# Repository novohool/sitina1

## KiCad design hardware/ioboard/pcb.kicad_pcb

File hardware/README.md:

# HARDWARE

This folder contains all the PCB design files and 3D models for the Sitina project.

## File List

* `auxiliary/` - Auxiliary PCB design files used for production testing, validation, and other purposes.
  * `jtag_adapter/` - A small JTAG adapter for connecting the IO board to a JTAG programmer.
  * `Resonant_V_validation/` - A separate board for testing the resonant V driver used in r0.11
  * `SR_V_validation/` - A separate board for testing the controlled slew-rate & dead-time V driver in r0.9
* `enclosure/` - 3D models for the enclosure in SolidWorks format.
* `gripflex/` - grip handle flexible PCB design files.
* `gripflex-lh/` - Left handed version
* `ioboard/` - IO board (power supply, routing, house keeping MCU, etc) PCB design files.
* `ioboard-lh/` - Left handed version
* `sensorboard/` - Latest Sensor board (CCD Sensor, AFE, H/V Driver, Controller) PCB design files
* `sensorboard-backport/` - Sensor board PCB design files. This version is a back port of r0.11 to r0.9. Uses the old H/V Drivers
* `pcb_common/` - Symbol and footprint libraries. This is a submodule link to: [pcb_common](https://gitlab.com/zephray/pcb_common)

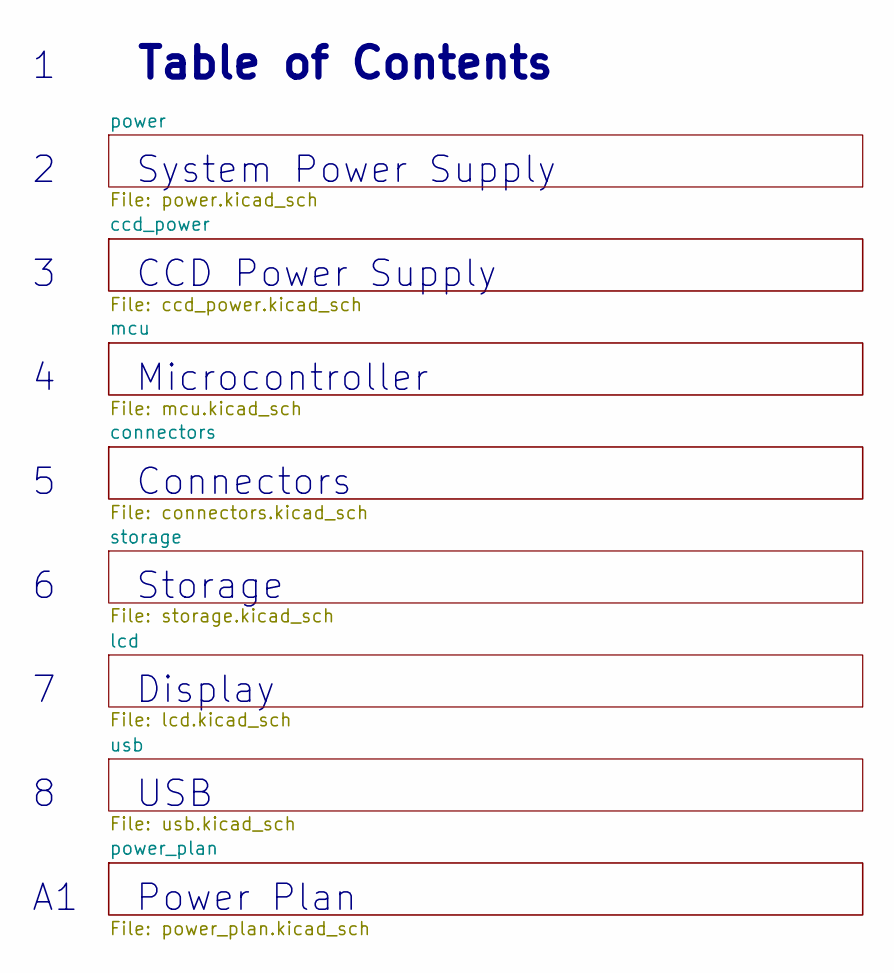
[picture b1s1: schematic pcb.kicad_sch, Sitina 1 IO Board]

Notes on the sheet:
CCD Power Supply
Power Plan
System Power Supply
Table of Contents
USB
Microcontroller
Display
Storage
Connectors

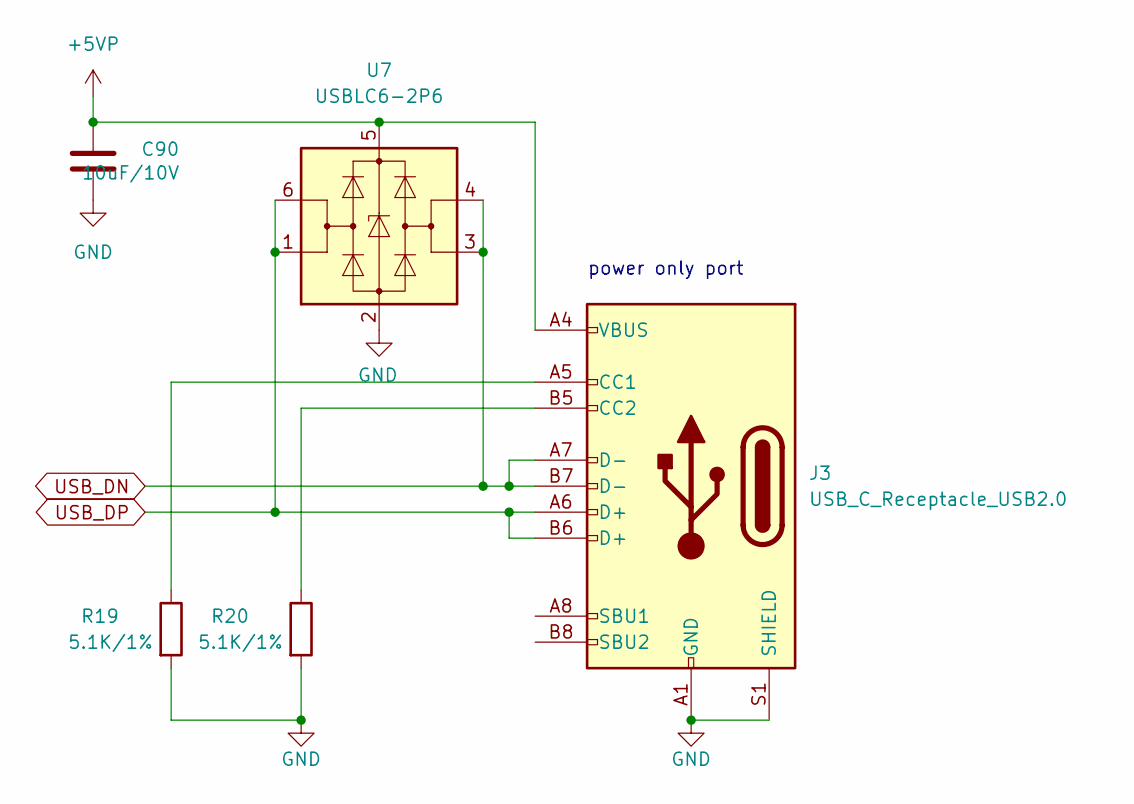
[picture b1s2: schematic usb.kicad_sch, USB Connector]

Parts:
C90: 10uF/10V; C_0603_1608Metric
J3: USB_C_Receptacle_USB2.0; USB_C_Receptacle_HRO_TYPE-C-31-M-12
R19, R20: 5.1K/1%; R_0402_1005Metric
U7: USBLC6-2P6; SOT-666

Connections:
+5VP: C90.1, J3.A4 (VBUS), J3.A9 (VBUS), J3.B4 (VBUS), J3.B9 (VBUS), U7.5 (VBUS); also elsewhere on the board
GND: C90.2, J3.A1 (GND), J3.A12 (GND), J3.B1 (GND), J3.B12 (GND), J3.S1 (SHIELD), R19.2, R20.2, U7.2 (GND); also elsewhere on the board
unnamed: J3.A5 (CC1), R19.1
unnamed: J3.B5 (CC2), R20.1
USB_DN: J3.A7 (D-), J3.B7 (D-), U7.3 (I/O2), U7.4 (I/O2); also elsewhere on the board
USB_DP: J3.A6 (D+), J3.B6 (D+), U7.1 (I/O1), U7.6 (I/O1); also elsewhere on the board

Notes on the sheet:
power only port

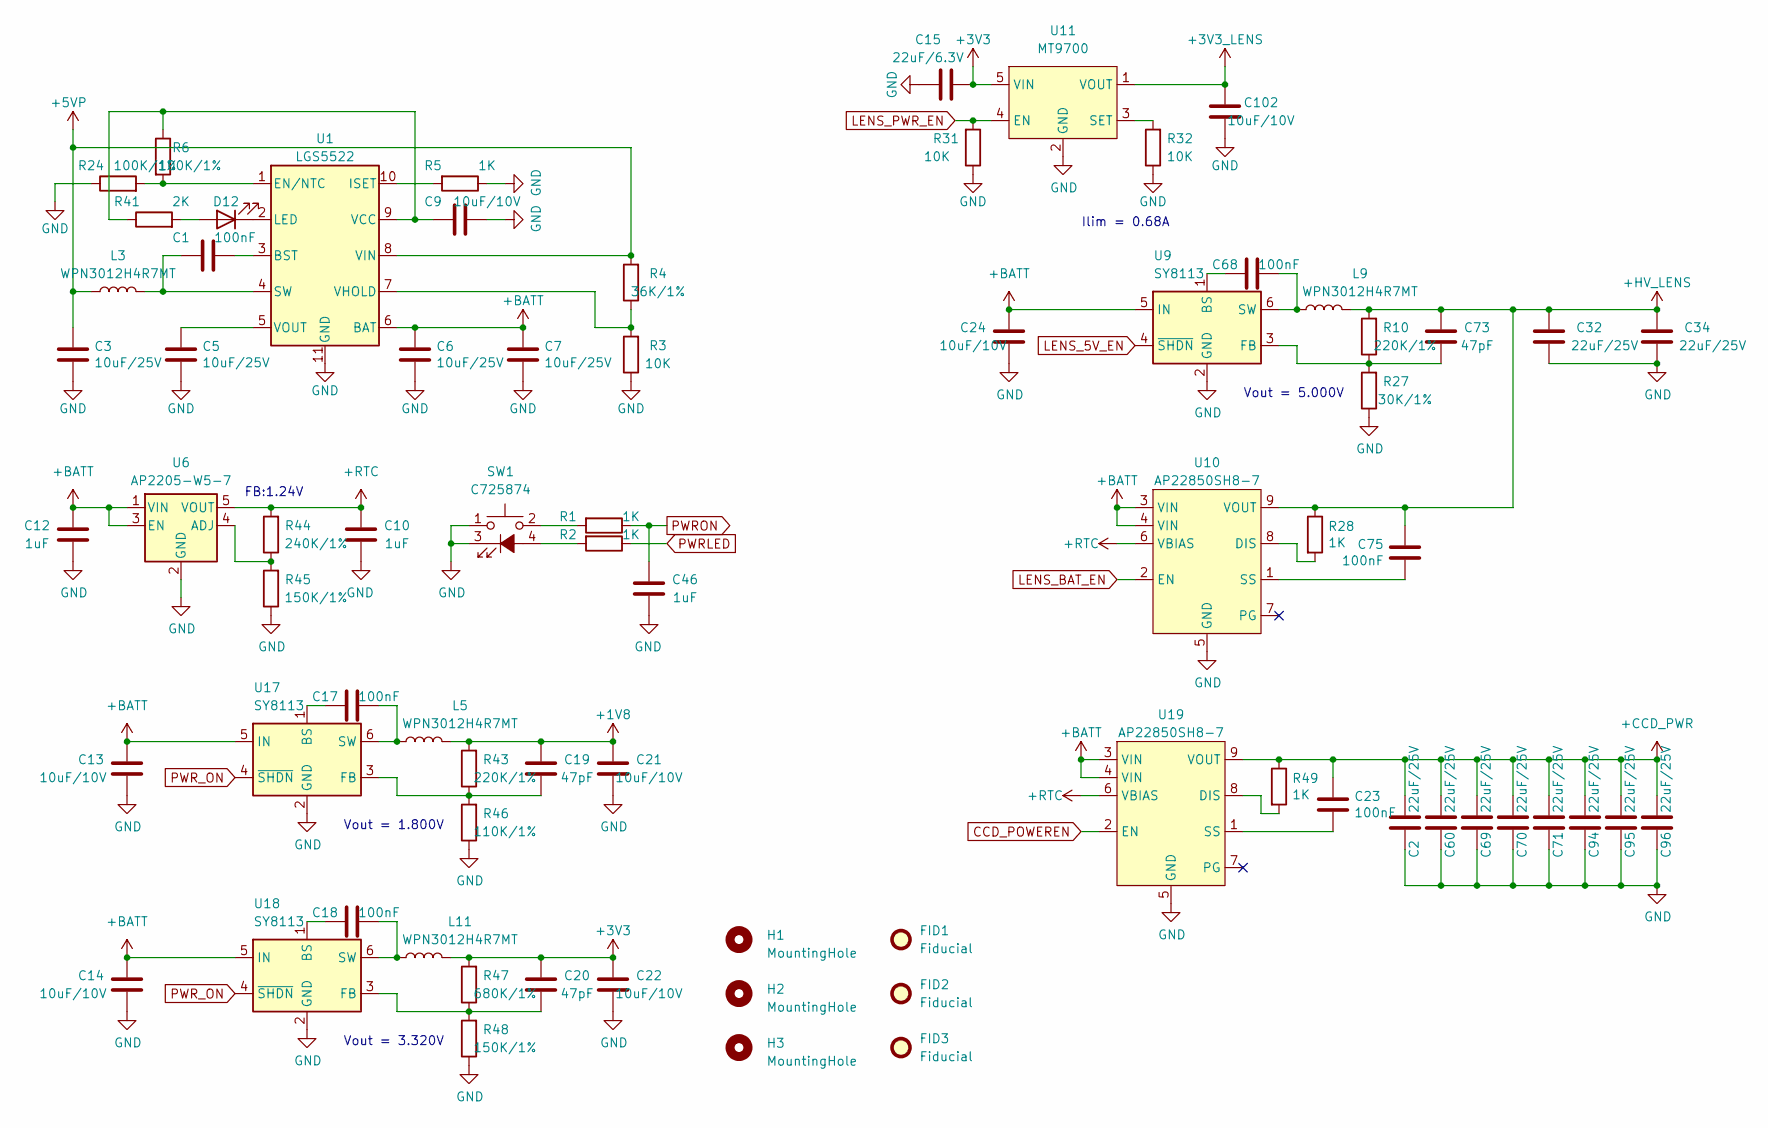
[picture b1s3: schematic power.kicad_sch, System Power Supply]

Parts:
C1, C17, C18, C23, C68, C75: 100nF; C_0402_1005Metric
C2, C32, C34, C60, C69, C70, C71, C94, C95, C96: 22uF/25V; C_1206_3216Metric
C3, C5, C6, C7: 10uF/25V; C_0805_2012Metric
C9, C13, C14, C21, C22, C24, C102: 10uF/10V; C_0603_1608Metric
C10, C12, C46: 1uF; C_0402_1005Metric
C15: 22uF/6.3V; C_0603_1608Metric
C19, C20, C73: 47pF; C_0402_1005Metric
D12: LED; LED_0603_1608Metric
FID1, FID2, FID3: Fiducial; Fiducial_0.75mm_Mask1.5mm
H1, H2, H3: MountingHole; MountingHole_2.2mm_M2_DIN965
L3, L5, L9, L11: WPN3012H4R7MT; L_Changjiang_FNR3012S
R1, R2, R5, R28, R49: 1K; R_0402_1005Metric
R3, R31, R32: 10K; R_0402_1005Metric
R4: 36K/1%; R_0402_1005Metric
R6, R24: 100K/1%; R_0402_1005Metric
R10, R43: 220K/1%; R_0402_1005Metric
R27: 30K/1%; R_0402_1005Metric
R41: 2K; R_0402_1005Metric
R44: 240K/1%; R_0402_1005Metric
R45, R48: 150K/1%; R_0402_1005Metric
R46: 110K/1%; R_0402_1005Metric
R47: 680K/1%; R_0402_1005Metric
SW1: C725874; TM-007-D1-X
U1: LGS5522; SSOP-10-1EP_3.9x4.9mm_P1mm_EP2.1x3.3mm
U6: AP2205-W5-7; SOT-23-5
U9, U17, U18: SY8113; TSOT-23-6
U10, U19: AP22850SH8-7; DFN-8-1EP_2x2mm_P0.5mm_EP0.9x1.6mm
U11: MT9700; SOT-23-5

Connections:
+1V8: C19.2, C21.2, L5.2, R43.2; also elsewhere on the board
+3V3: C15.1, C20.2, C22.2, L11.2, R47.2, U11.5 (VIN); also elsewhere on the board
+3V3_LENS: C102.1, U11.1 (VOUT); also elsewhere on the board
+5VP: C3.2, L3.1, R4.2, U1.8 (VIN); also elsewhere on the board
+BATT: C6.2, C7.2, C12.1, C13.2, C14.2, C24.2, U1.6 (BAT), U6.1 (VIN), U6.3 (EN), U9.5 (IN), U10.3 (VIN), U10.4 (VIN), U17.5 (IN), U18.5 (IN), U19.3 (VIN), U19.4 (VIN); also elsewhere on the board
+CCD_PWR: C2.1, C23.2, C60.1, C69.1, C70.1, C71.1, C94.1, C95.1, C96.1, R49.1, U19.9 (VOUT); also elsewhere on the board
+HV_LENS: C32.1, C34.1, C73.2, C75.2, L9.2, R10.2, R28.1, U10.9 (VOUT); also elsewhere on the board
+RTC: C10.1, R44.2, U6.5 (VOUT), U10.6 (VBIAS), U19.6 (VBIAS); also elsewhere on the board
CCD_POWEREN: U19.2 (EN); also elsewhere on the board
GND: C2.2, C3.1, C5.1, C6.1, C7.1, C9.1, C10.2, C12.2, C13.1, C14.1, C15.2, C21.1, C22.1, C24.1, C32.2, C34.2, C46.2, C60.2, C69.2, C70.2, C71.2, C94.2, C95.2, C96.2, C102.2, R3.1, R5.1, R24.1, R27.1, R31.1, R32.1, R45.1, R46.1, R48.1, SW1.1, SW1.3 (K), U1.11 (GND), U6.2 (GND), U9.2 (GND), U10.5 (GND), U11.2 (GND), U17.2 (GND), U18.2 (GND), U19.5 (GND); also elsewhere on the board
LENS_5V_EN: U9.4 (~SHDN); also elsewhere on the board
LENS_BAT_EN: U10.2 (EN); also elsewhere on the board
LENS_PWR_EN: R31.2, U11.4 (EN); also elsewhere on the board
unnamed: D12.2 (A), R41.2
unnamed: D12.1 (K), U1.2 (LED)
unnamed: R1.2, SW1.2
unnamed: R2.2, SW1.4 (A)
unnamed: C1.1, U1.3 (BST)
unnamed: R6.2, R24.2, U1.1 (EN/NTC)
unnamed: R5.2, U1.10 (ISET)
unnamed: C1.2, L3.2, U1.4 (SW)
unnamed: C9.2, R6.1, R41.1, U1.9 (VCC)
unnamed: R3.2, R4.1, U1.7 (VHOLD)
unnamed: C5.2, U1.5 (VOUT)
unnamed: R44.1, R45.2, U6.4 (ADJ)
unnamed: C68.2, U9.1 (BS)
unnamed: C73.1, R10.1, R27.2, U9.3 (FB)
unnamed: C68.1, L9.1, U9.6 (SW)
unnamed: R28.2, U10.8 (DIS)
unnamed: C75.1, U10.1 (SS)
unnamed: R32.2, U11.3 (SET)
unnamed: C17.2, U17.1 (BS)
unnamed: C19.1, R43.1, R46.2, U17.3 (FB)
unnamed: C17.1, L5.1, U17.6 (SW)
unnamed: C18.2, U18.1 (BS)
unnamed: C20.1, R47.1, R48.2, U18.3 (FB)
unnamed: C18.1, L11.1, U18.6 (SW)
unnamed: R49.2, U19.8 (DIS)
unnamed: C23.1, U19.1 (SS)
PWRLED: R2.1; also elsewhere on the board
PWRON: C46.1, R1.1; also elsewhere on the board
PWR_ON: U17.4 (~SHDN), U18.4 (~SHDN); also elsewhere on the board

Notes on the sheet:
Ilim = 0.68A
Vout = 1.800V
Vout = 3.320V
FB:1.24V
Vout = 5.000V

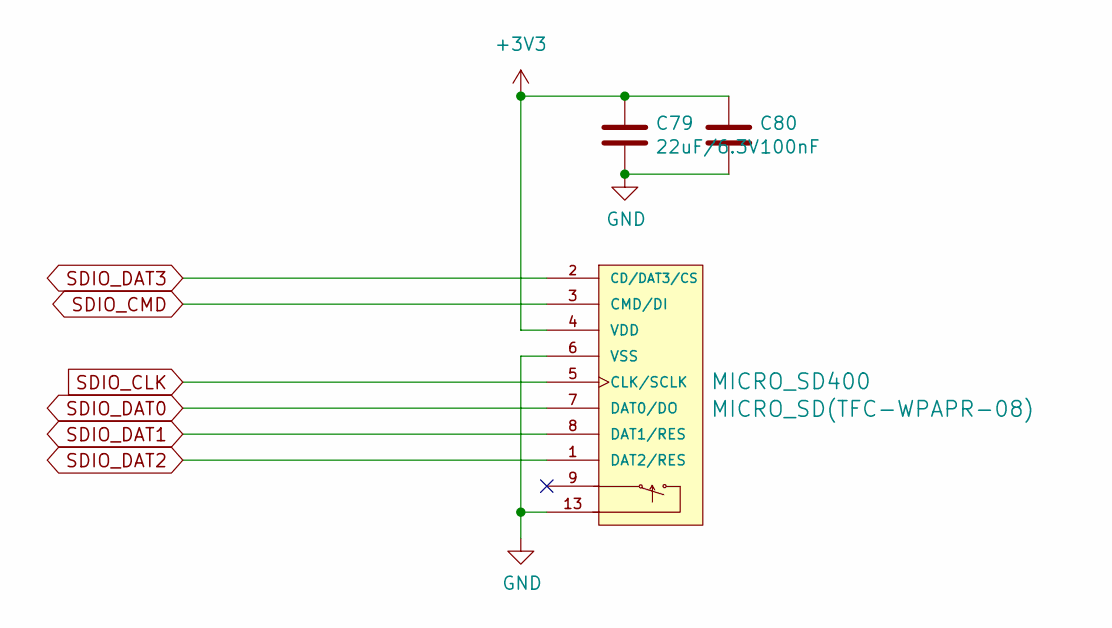
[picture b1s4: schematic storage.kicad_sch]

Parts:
C79: 22uF/6.3V; C_0603_1608Metric
C80: 100nF; C_0402_1005Metric
MICRO_SD400: MICRO_SD(TFC-WPAPR-08); TFC-WPAPR-08

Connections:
+3V3: C79.1, C80.1; also elsewhere on the board
GND: C79.2, C80.2; also elsewhere on the board

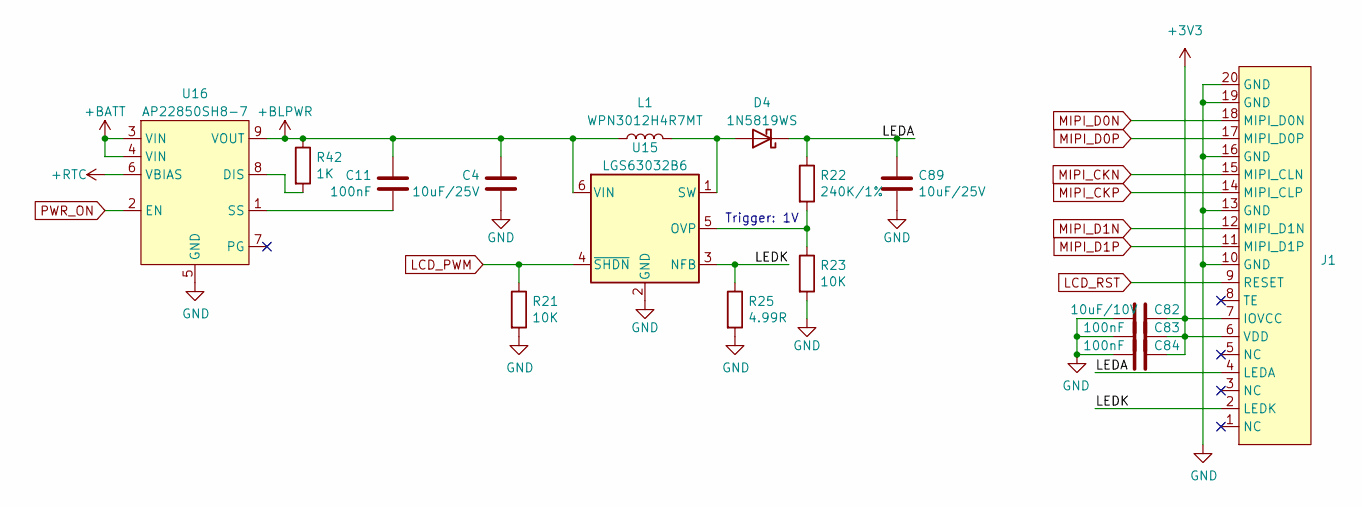
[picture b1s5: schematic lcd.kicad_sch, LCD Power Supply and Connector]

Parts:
C4, C89: 10uF/25V; C_0805_2012Metric
C11, C83, C84: 100nF; C_0402_1005Metric
C82: 10uF/10V; C_0603_1608Metric
D4: 1N5819WS; D_SOD-323
J1: Hirose_FH12-20S-0.5SH_1x20-1MP_P0.50mm_Horizontal_Reversed
L1: WPN3012H4R7MT; L_Changjiang_FNR3012S
R21, R23: 10K; R_0402_1005Metric
R22: 240K/1%; R_0402_1005Metric
R25: 4.99R; R_0402_1005Metric
R42: 1K; R_0402_1005Metric
U15: LGS63032B6; SOT-23-6
U16: AP22850SH8-7; DFN-8-1EP_2x2mm_P0.5mm_EP0.9x1.6mm

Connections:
+3V3: C82.2, C83.1, C84.1, J1.6 (VDD), J1.7 (IOVCC); also elsewhere on the board
+BATT: U16.3 (VIN), U16.4 (VIN); also elsewhere on the board
+BLPWR: C4.2, C11.2, L1.1, R42.1, U15.6 (VIN), U16.9 (VOUT)
+RTC: U16.6 (VBIAS); also elsewhere on the board
/lcd/LEDA: C89.2, D4.1 (K), J1.4 (LEDA), R22.1
/lcd/LEDK: J1.2 (LEDK), R25.1, U15.3 (NFB)
GND: C4.1, C82.1, C83.2, C84.2, C89.1, J1.10 (GND), J1.13 (GND), J1.16 (GND), J1.19 (GND), J1.20 (GND), R21.2, R23.2, R25.2, U15.2 (GND), U16.5 (GND); also elsewhere on the board
LCD_PWM: R21.1, U15.4 (~SHDN); also elsewhere on the board
LCD_RST: J1.9 (RESET); also elsewhere on the board
MIPI_CKN: J1.15 (MIPI_CLN); also elsewhere on the board
MIPI_CKP: J1.14 (MIPI_CLP); also elsewhere on the board
MIPI_D0N: J1.18 (MIPI_D0N); also elsewhere on the board
MIPI_D0P: J1.17 (MIPI_D0P); also elsewhere on the board
MIPI_D1N: J1.12 (MIPI_D1N); also elsewhere on the board
MIPI_D1P: J1.11 (MIPI_D1P); also elsewhere on the board
unnamed: D4.2 (A), L1.2, U15.1 (SW)
unnamed: R22.2, R23.1, U15.5 (OVP)
unnamed: R42.2, U16.8 (DIS)
unnamed: C11.1, U16.1 (SS)
PWR_ON: U16.2 (EN); also elsewhere on the board

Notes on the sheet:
Trigger: 1V

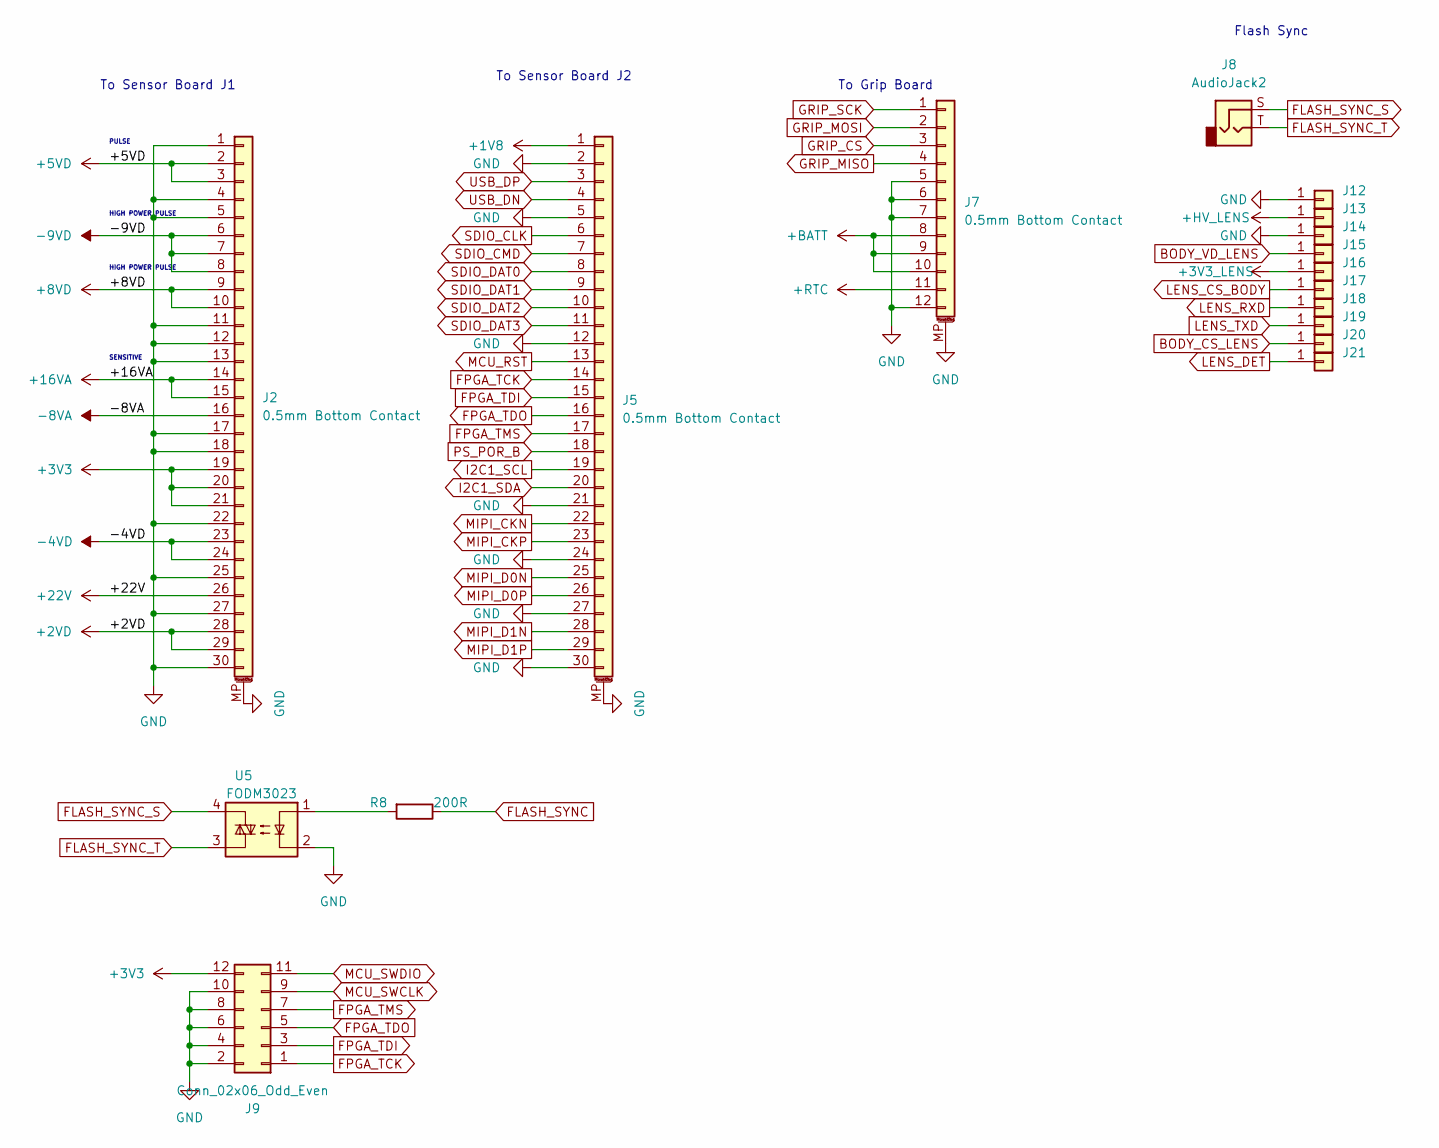
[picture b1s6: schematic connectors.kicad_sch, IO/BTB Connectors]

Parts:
J2, J5: 0.5mm Bottom Contact; Hirose_FH12-30S-0.5SH_1x30-1MP_P0.50mm_Horizontal
J7: 0.5mm Bottom Contact; Hirose_FH12-12S-0.5SH_1x12-1MP_P0.50mm_Horizontal
J8: AudioJack2; Jack_2.5mm_PJ_210A
J9: Conn_02x06_Odd_Even; PinSocket_2x06_P1.27mm_Horizontal
J12, J13, J14, J15, J16, J17, J18, J19, J20, J21: LensMount; YZP0652-15072-01
R8: 200R; R_0402_1005Metric
U5: FODM3023; MFP4_3.85x4.4

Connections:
+1V8: J5.1; also elsewhere on the board
+2VD: J2.28, J2.29; also elsewhere on the board
+3V3: J2.19, J2.20, J2.21, J9.12; also elsewhere on the board
+3V3_LENS: J16.1; also elsewhere on the board
+5VD: J2.2, J2.3; also elsewhere on the board
+8VD: J2.9, J2.10; also elsewhere on the board
+16VA: J2.14, J2.15; also elsewhere on the board
+22V: J2.26; also elsewhere on the board
+BATT: J7.8, J7.9, J7.10; also elsewhere on the board
+HV_LENS: J13.1; also elsewhere on the board
+RTC: J7.11; also elsewhere on the board
-4VD: J2.23, J2.24; also elsewhere on the board
-8VA: J2.16; also elsewhere on the board
-9VD: J2.6, J2.7, J2.8; also elsewhere on the board
BODY_CS_LENS: J20.1; also elsewhere on the board
BODY_VD_LENS: J15.1; also elsewhere on the board
FLASH_SYNC: R8.1; also elsewhere on the board
FLASH_SYNC_S: J8.S, U5.4
FLASH_SYNC_T: J8.T, U5.3
FPGA_TCK: J5.14, J9.1
FPGA_TDI: J5.15, J9.3
FPGA_TDO: J5.16, J9.5
FPGA_TMS: J5.17, J9.7
GND: J2.1, J2.4, J2.5, J2.11, J2.12, J2.13, J2.17, J2.18, J2.22, J2.25, J2.27, J2.30, J2.MP (MountPin), J5.2, J5.5, J5.12, J5.21, J5.24, J5.27, J5.30, J5.MP (MountPin), J7.5, J7.6, J7.7, J7.12, J7.MP (MountPin), J9.2, J9.4, J9.6, J9.8, J9.10, J12.1, J14.1, U5.2; also elsewhere on the board
GRIP_CS: J7.3; also elsewhere on the board
GRIP_MISO: J7.4; also elsewhere on the board
GRIP_MOSI: J7.2; also elsewhere on the board
GRIP_SCK: J7.1; also elsewhere on the board
I2C1_SCL: J5.19; also elsewhere on the board
I2C1_SDA: J5.20; also elsewhere on the board
LENS_CS_BODY: J17.1; also elsewhere on the board
LENS_DET: J21.1; also elsewhere on the board
LENS_RXD: J18.1; also elsewhere on the board
LENS_TXD: J19.1; also elsewhere on the board
MCU_BOOT: J9.9; also elsewhere on the board
MCU_RST: J5.13; also elsewhere on the board
MCU_SWDIO: J9.11; also elsewhere on the board
MIPI_CKN: J5.22; also elsewhere on the board
MIPI_CKP: J5.23; also elsewhere on the board
MIPI_D0N: J5.25; also elsewhere on the board
MIPI_D0P: J5.26; also elsewhere on the board
MIPI_D1N: J5.28; also elsewhere on the board
MIPI_D1P: J5.29; also elsewhere on the board
unnamed: R8.2, U5.1
PS_POR_B: J5.18; also elsewhere on the board
SDIO_CLK: J5.6; also elsewhere on the board
SDIO_CMD: J5.7; also elsewhere on the board
SDIO_DAT0: J5.8; also elsewhere on the board
SDIO_DAT1: J5.9; also elsewhere on the board
SDIO_DAT2: J5.10; also elsewhere on the board
SDIO_DAT3: J5.11; also elsewhere on the board
USB_DN: J5.4; also elsewhere on the board
USB_DP: J5.3; also elsewhere on the board

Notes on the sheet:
PULSE
To Sensor Board J2
To Grip Board
To Sensor Board J1
Flash Sync
SENSITIVE
HIGH POWER PULSE

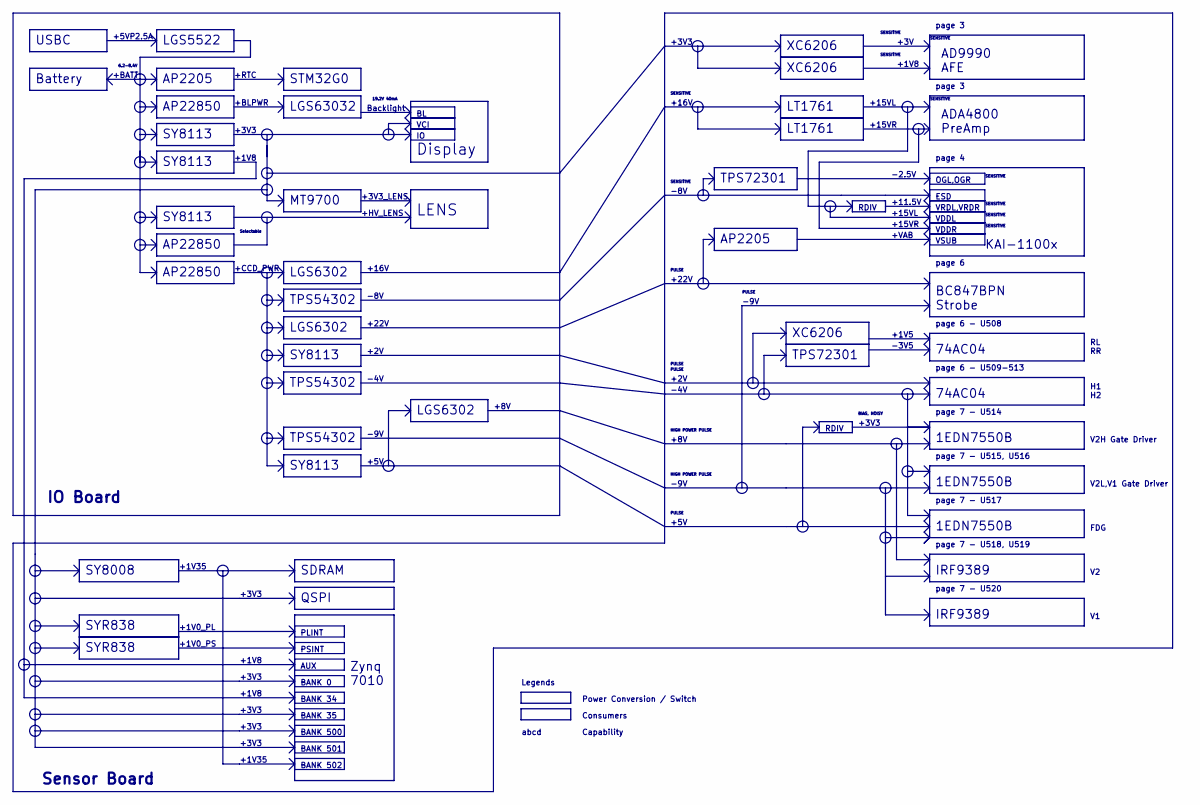
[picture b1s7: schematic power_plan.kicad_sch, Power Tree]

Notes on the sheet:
MT9700
page 7 - U515, U516
+16V
+3V3
SENSITIVE
HIGH POWER PULSE
+1V8
+15VL
page 6 - U508
+1V0_PL
+15VR
Consumers
LGS5522
SY8113
TPS54302
VCI
PLINT
STM32G0
+1V5
+RTC
2.5A
page 6 - U509-513
ESD
-9V
VDDR
LT1761
BANK 501
Legends
+8V
Zynq 7010
+CCD_PWR
+1V35
6.2-8.4V
+2V
Capability
LGS6302
PULSE
-4V
1EDN7550B
ADA4800 PreAmp

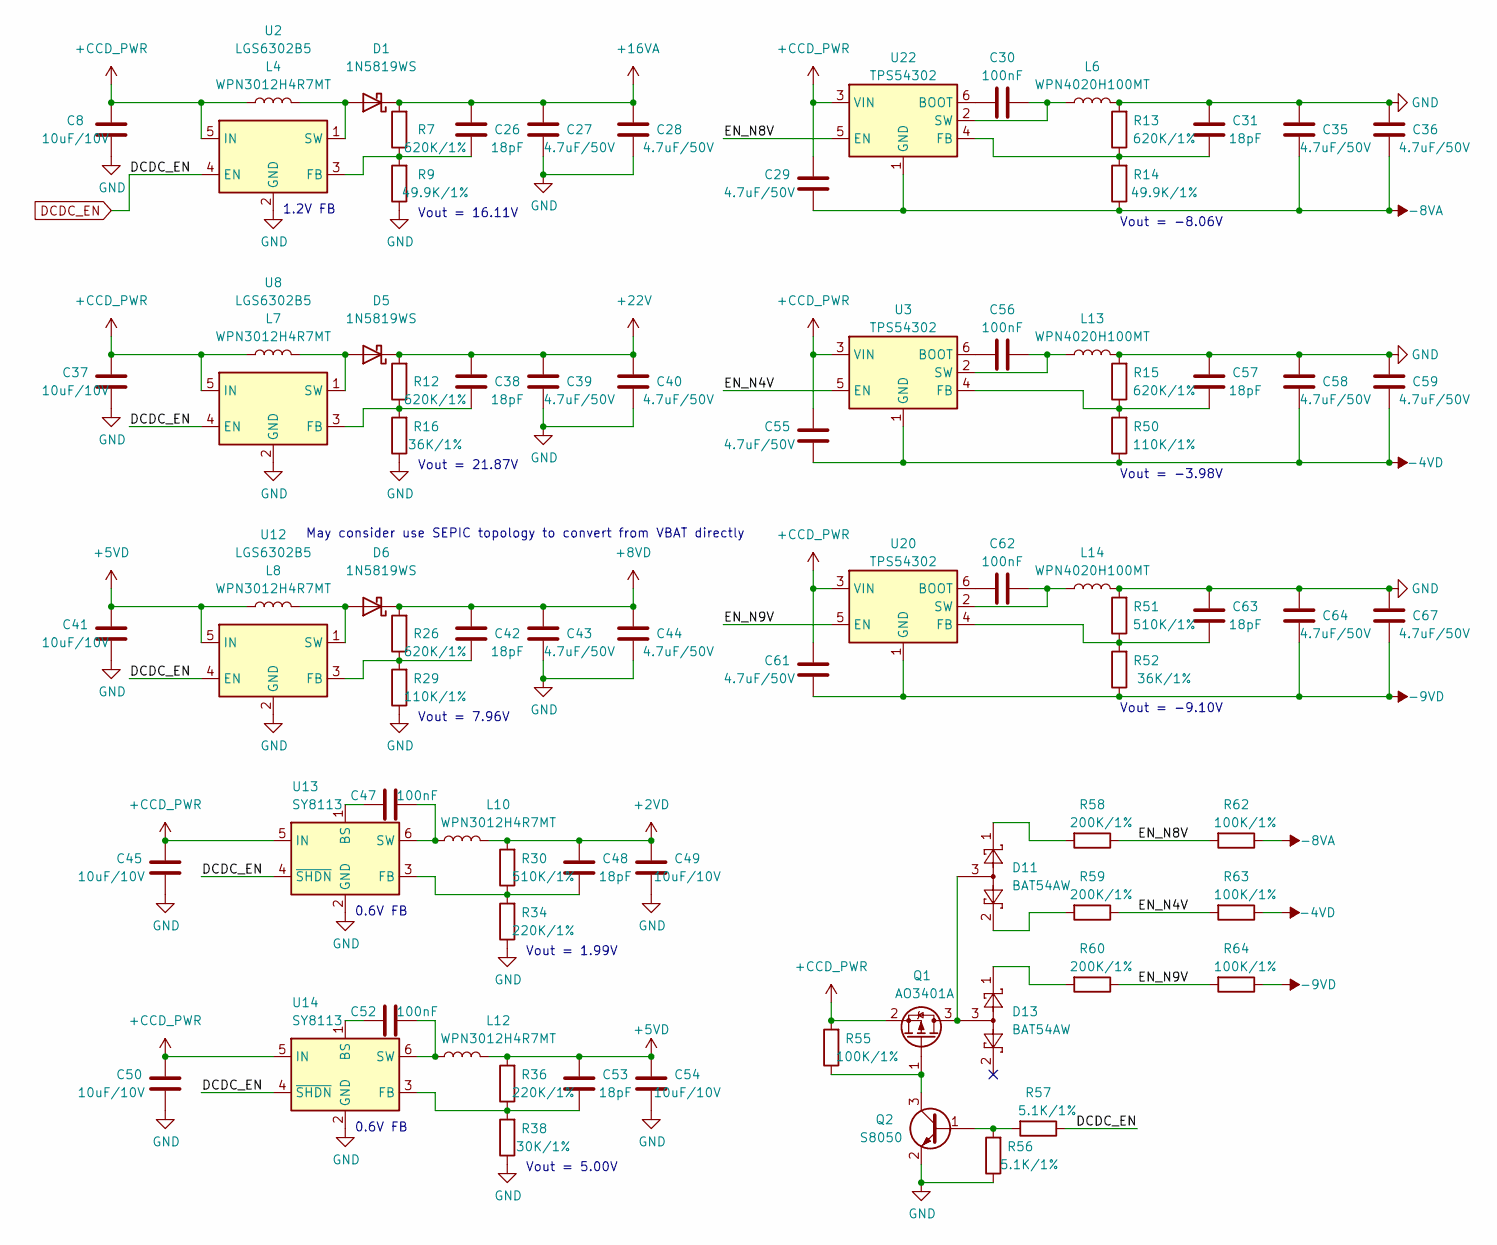
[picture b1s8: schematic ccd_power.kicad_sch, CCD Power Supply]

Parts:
C8, C37, C41, C45, C49, C50, C54: 10uF/10V; C_0603_1608Metric
C26, C31, C38, C42, C48, C53, C57, C63: 18pF; C_0402_1005Metric
C27, C28, C29, C35, C36, C39, C40, C43, C44, C55, C58, C59, C61, C64, C67: 4.7uF/50V; C_0805_2012Metric
C30, C47, C52, C56, C62: 100nF; C_0402_1005Metric
D1, D5, D6: 1N5819WS; D_SOD-323
D11, D13: BAT54AW; SOT-323_SC-70
L4, L7, L8, L10, L12: WPN3012H4R7MT; L_Changjiang_FNR3012S
L6, L13, L14: WPN4020H100MT; L_Changjiang_FNR4020S
Q1: AO3401A; SOT-23
Q2: S8050; SOT-23
R7, R12, R13, R15, R26: 620K/1%; R_0402_1005Metric
R9, R14: 49.9K/1%; R_0402_1005Metric
R16, R52: 36K/1%; R_0402_1005Metric
R29, R50: 110K/1%; R_0402_1005Metric
R30, R51: 510K/1%; R_0402_1005Metric
R34, R36: 220K/1%; R_0402_1005Metric
R38: 30K/1%; R_0402_1005Metric
R55, R62, R63, R64: 100K/1%; R_0402_1005Metric
R56, R57: 5.1K/1%; R_0402_1005Metric
R58, R59, R60: 200K/1%; R_0402_1005Metric
U2, U8, U12: LGS6302B5; SOT-23-5
U3, U20, U22: TPS54302; SOT-23-6
U13, U14: SY8113; TSOT-23-6

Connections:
+2VD: C48.2, C49.2, L10.2, R30.2; also elsewhere on the board
+5VD: C41.2, C53.2, C54.2, L8.1, L12.2, R36.2, U12.5 (IN); also elsewhere on the board
+8VD: C42.2, C43.2, C44.2, D6.1 (K), R26.2; also elsewhere on the board
+16VA: C26.2, C27.2, C28.2, D1.1 (K), R7.2; also elsewhere on the board
+22V: C38.2, C39.2, C40.2, D5.1 (K), R12.2; also elsewhere on the board
+CCD_PWR: C8.2, C29.2, C37.2, C45.2, C50.2, C55.2, C61.2, L4.1, L7.1, Q1.2 (S), R55.2, U2.5 (IN), U3.3 (VIN), U8.5 (IN), U13.5 (IN), U14.5 (IN), U20.3 (VIN), U22.3 (VIN); also elsewhere on the board
-4VD: C55.1, C58.1, C59.1, R50.1, R63.1, U3.1 (GND); also elsewhere on the board
-8VA: C29.1, C35.1, C36.1, R14.1, R62.1, U22.1 (GND); also elsewhere on the board
-9VD: C61.1, C64.1, C67.1, R52.1, R64.1, U20.1 (GND); also elsewhere on the board
/ccd_power/EN_N4V: R59.1, R63.2, U3.5 (EN)
/ccd_power/EN_N8V: R58.1, R62.2, U22.5 (EN)
/ccd_power/EN_N9V: R60.1, R64.2, U20.5 (EN)
DCDC_EN: R57.1, U2.4 (EN), U8.4 (EN), U12.4 (EN), U13.4 (~SHDN), U14.4 (~SHDN); also elsewhere on the board
GND: C8.1, C27.1, C28.1, C31.2, C35.2, C36.2, C37.1, C39.1, C40.1, C41.1, C43.1, C44.1, C45.1, C49.1, C50.1, C54.1, C57.2, C58.2, C59.2, C63.2, C64.2, C67.2, L6.2, L13.2, L14.2, Q2.2 (E), R9.1, R13.2, R15.2, R16.1, R29.1, R34.1, R38.1, R51.2, R56.1, U2.2 (GND), U8.2 (GND), U12.2 (GND), U13.2 (GND), U14.2 (GND); also elsewhere on the board
unnamed: D1.2 (A), L4.2, U2.1 (SW)
unnamed: D5.2 (A), L7.2, U8.1 (SW)
unnamed: D6.2 (A), L8.2, U12.1 (SW)
unnamed: D11.1, R58.2
unnamed: D11.2, R59.2
unnamed: D13.1, R60.2
unnamed: D11.3, D13.3, Q1.3 (D)
unnamed: Q1.1 (G), Q2.3 (C), R55.1
unnamed: Q2.1 (B), R56.2, R57.2
unnamed: C26.1, R7.1, R9.2, U2.3 (FB)
unnamed: C56.2, U3.6 (BOOT)
unnamed: C57.1, R15.1, R50.2, U3.4 (FB)
unnamed: C56.1, L13.1, U3.2 (SW)
unnamed: C38.1, R12.1, R16.2, U8.3 (FB)
unnamed: C42.1, R26.1, R29.2, U12.3 (FB)
unnamed: C47.2, U13.1 (BS)
unnamed: C48.1, R30.1, R34.2, U13.3 (FB)
unnamed: C47.1, L10.1, U13.6 (SW)
unnamed: C52.2, U14.1 (BS)
unnamed: C53.1, R36.1, R38.2, U14.3 (FB)
unnamed: C52.1, L12.1, U14.6 (SW)
unnamed: C62.2, U20.6 (BOOT)
unnamed: C63.1, R51.1, R52.2, U20.4 (FB)
unnamed: C62.1, L14.1, U20.2 (SW)
unnamed: C30.2, U22.6 (BOOT)
unnamed: C31.1, R13.1, R14.2, U22.4 (FB)
unnamed: C30.1, L6.1, U22.2 (SW)

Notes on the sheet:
Vout = -8.06V
0.6V FB
May consider use SEPIC topology to convert from VBAT directly
1.2V FB
Vout = 7.96V
Vout = 21.87V
Vout = -9.10V
Vout = 16.11V
Vout = 1.99V
Vout = 5.00V
Vout = -3.98V

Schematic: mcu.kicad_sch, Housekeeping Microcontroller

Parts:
BZ1: Buzzer; Buzzer_Murata_PKMCS0909E
C33: 22uF/6.3V; C_0603_1608Metric
C65, C66: 18pF; C_0402_1005Metric
C72, C92: 100nF; C_0402_1005Metric
R11, R18: 10K; R_0402_1005Metric
R33, R37: 1K; R_0402_1005Metric
R39, R40: 2K; R_0402_1005Metric
U4: STM32G030K6Tx; LQFP-32_7x7mm_P0.8mm
Y2: 32.768K; Crystal_SMD_TXC_9HT11-2Pin_2.0x1.2mm_HandSoldering

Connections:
+3V3: R39.1, R40.1; also elsewhere on the board
+RTC: C33.1, C92.1, R11.1, U4.4 (VDD); also elsewhere on the board
/mcu/BEEPER: R37.2, U4.27 (PB3)
BODY_CS_LENS: U4.29 (PB5); also elsewhere on the board
BODY_VD_LENS: U4.15 (PB0); also elsewhere on the board
CCD_POWEREN: U4.17 (PB2); also elsewhere on the board
DCDC_EN: U4.16 (PB1); also elsewhere on the board
FLASH_SYNC: U4.1 (PB9); also elsewhere on the board
GND: BZ1.2 (-), C33.2, C65.1, C66.1, C72.1, C92.2, R18.1, U4.5 (VSS); also elsewhere on the board
GRIP_CS: U4.11 (PA4); also elsewhere on the board
GRIP_MISO: U4.13 (PA6); also elsewhere on the board
GRIP_MOSI: U4.14 (PA7); also elsewhere on the board
GRIP_SCK: U4.12 (PA5); also elsewhere on the board
I2C1_SCL: R40.2, U4.30 (PB6); also elsewhere on the board
I2C1_SDA: R39.2, U4.31 (PB7); also elsewhere on the board
LCD_PWM: U4.28 (PB4); also elsewhere on the board
LCD_RST: U4.21 (PA10/NC); also elsewhere on the board
LENS_5V_EN: U4.19 (PA9/NC); also elsewhere on the board
LENS_BAT_EN: U4.23 (PA12/PA10); also elsewhere on the board
LENS_CS_BODY: U4.18 (PA8); also elsewhere on the board
LENS_DET: U4.7 (PA0); also elsewhere on the board
LENS_PWR_EN: U4.8 (PA1); also elsewhere on the board
LENS_RXD: U4.10 (PA3); also elsewhere on the board
LENS_TXD: U4.9 (PA2); also elsewhere on the board
MCU_BOOT: R18.2, U4.25 (PA14); also elsewhere on the board
MCU_RST: R33.1; also elsewhere on the board
MCU_SWDIO: U4.24 (PA13); also elsewhere on the board
unnamed: BZ1.1 (+), R37.1
unnamed: C72.2, R11.2, R33.2, U4.6 (NRST)
unnamed: C65.2, U4.2 (PC14), Y2.1
unnamed: C66.2, U4.3 (PC15), Y2.2
PS_POR_B: U4.22 (PA11/PA9); also elsewhere on the board
PWRLED: U4.32 (PB8); also elsewhere on the board
PWRON: U4.20 (PC6); also elsewhere on the board
PWR_ON: U4.26 (PA15); also elsewhere on the board

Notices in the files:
firmware/mcu/Core/Src/main.c:
Copyright (c) 2024 STMicroelectronics.
All rights reserved.
This software is licensed under terms that can be found in the LICENSE file
hardware/auxiliary/Resonant_V_validation/ccd_driver_v_adiabatic_simplified.kicad_sch:
Copyright 2024 Anhang Li, Wenting Zhang
This source describes Open Hardware and is licensed under the CERN-OHL-P v2.
hardware/gripflex/gripflex.kicad_pcb:
Copyright 2024 Wenting Zhang
hardware/ioboard/pcb.kicad_pcb:
This source describes Open Hardware and is licensed under the CERN-OHL-S v2.
